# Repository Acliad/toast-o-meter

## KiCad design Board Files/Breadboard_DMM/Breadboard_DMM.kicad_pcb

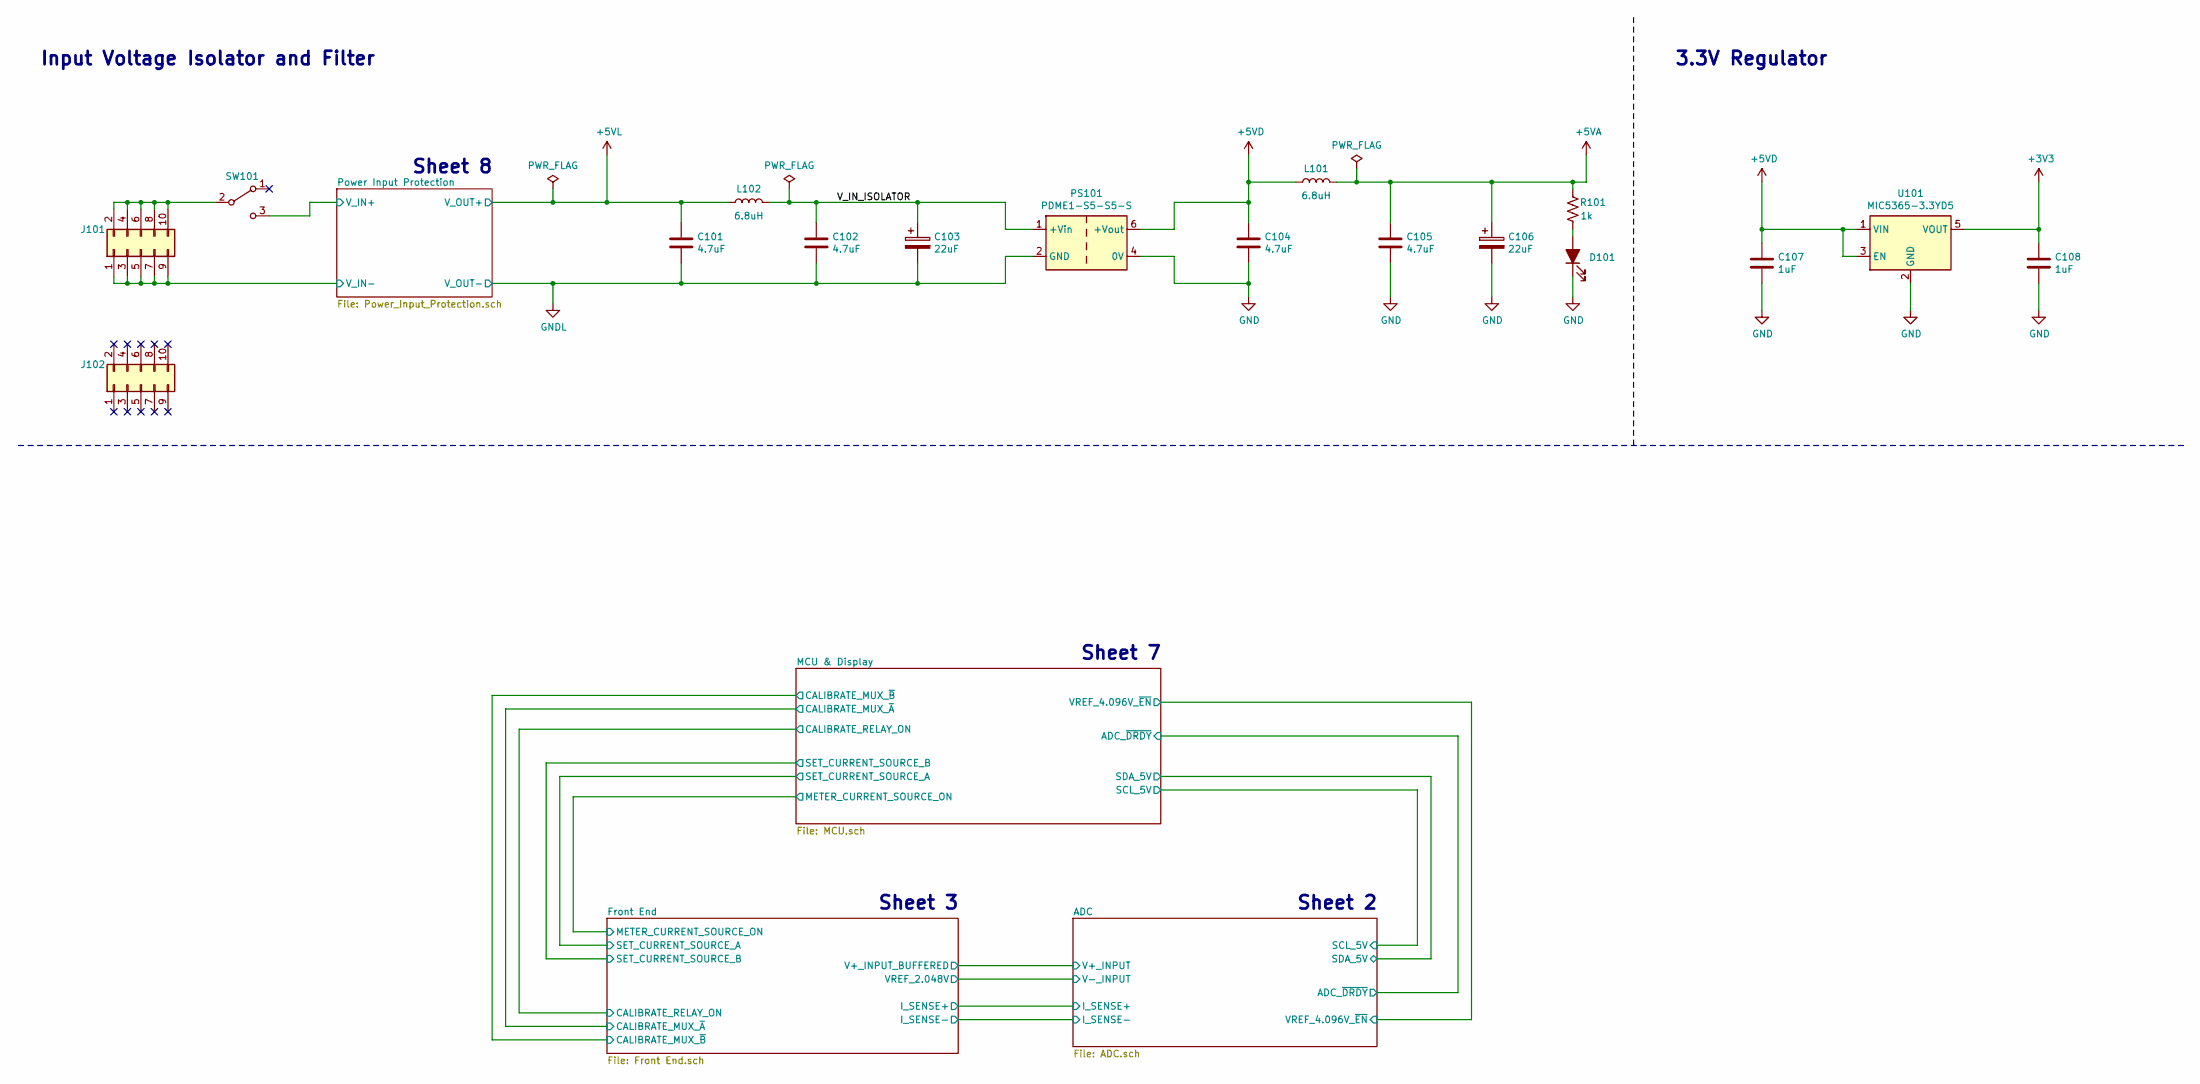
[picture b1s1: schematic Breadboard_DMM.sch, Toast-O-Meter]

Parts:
C101, C102, C104, C105: 4.7uF; C_0805_2012Metric_Pad1.18x1.45mm_HandSolder; Digi-Key PN 1276-6462-1-ND
C103, C106: 22uF; CP_Elec_5x5.3; Digi-Key PN 732-8505-1-ND
C107, C108: 1uF; C_0603_1608Metric_Pad1.08x0.95mm_HandSolder; Digi-Key PN 1276-6524-1-ND
D101: Pink; LED_Kingbright_AA3528V_3.5x2.8mm_handsolder; MPN AA3528VRVCS/A; Digi-Key PN 754-1534-1-ND
J101, J102: Conn_02x05_Odd_Even; PinHeader_2x05_P2.54mm_Vertical; Digi-Key PN 2057-PH2-10-UA-ND
L101, L102: 6.8uH; L_Taiyo-Yuden_NR-30xx_HandSoldering; Digi-Key PN 587-2592-1-ND
PS101: PDME1-S5-S5-S; CUI_DCDC-CONVERTER_PDME1-Sxx-S_1x4_P2.54mm_Drill1.0mm; MPN PDME1-S5-S5-S; Digi-Key PN 102-6320-ND
R101: 1k; R_0603_1608Metric_Pad1.05x0.95mm_HandSolder; Digi-Key PN 311-1.00KHRCT-ND
SW101: L102021ML04Q; SW_CuK_L102021ML04Q_SPDT_Angled; MPN L102021ML04Q; Digi-Key PN CKC5102-ND
U101: MIC5365-3.3YD5; SOT-23-5; Digi-Key PN 576-4085-1-ND

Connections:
+3V3: C108.1, U101.5 (VOUT); also elsewhere on the board
+5VA: C105.1, C106.1, L101.2, R101.1; also elsewhere on the board
+5VD: C104.1, C107.1, L101.1, PS101.6 (+Vout), U101.1 (VIN), U101.3 (EN); also elsewhere on the board
+5VL: C101.1, L102.1; also elsewhere on the board
/Power Input Protection/V_IN+: SW101.3 (C); also elsewhere on the board
/V_IN_ISOLATOR: C102.1, C103.1, L102.2, PS101.1 (+Vin)
GND: C104.2, C105.2, C106.2, C107.2, C108.2, D101.1 (K), PS101.4 (0V), U101.2 (GND); also elsewhere on the board
GNDL: C101.2, C102.2, C103.2, J101.1, J101.3, J101.5, J101.7, J101.9, PS101.2 (GND); also elsewhere on the board
unnamed: D101.2 (A), R101.2
unnamed: J101.2, J101.4, J101.6, J101.8, J101.10, SW101.2 (B)

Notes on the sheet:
Input Voltage Isolator and Filter
3.3V Regulator
Sheet 7
Sheet 2
Sheet 8
Sheet 3

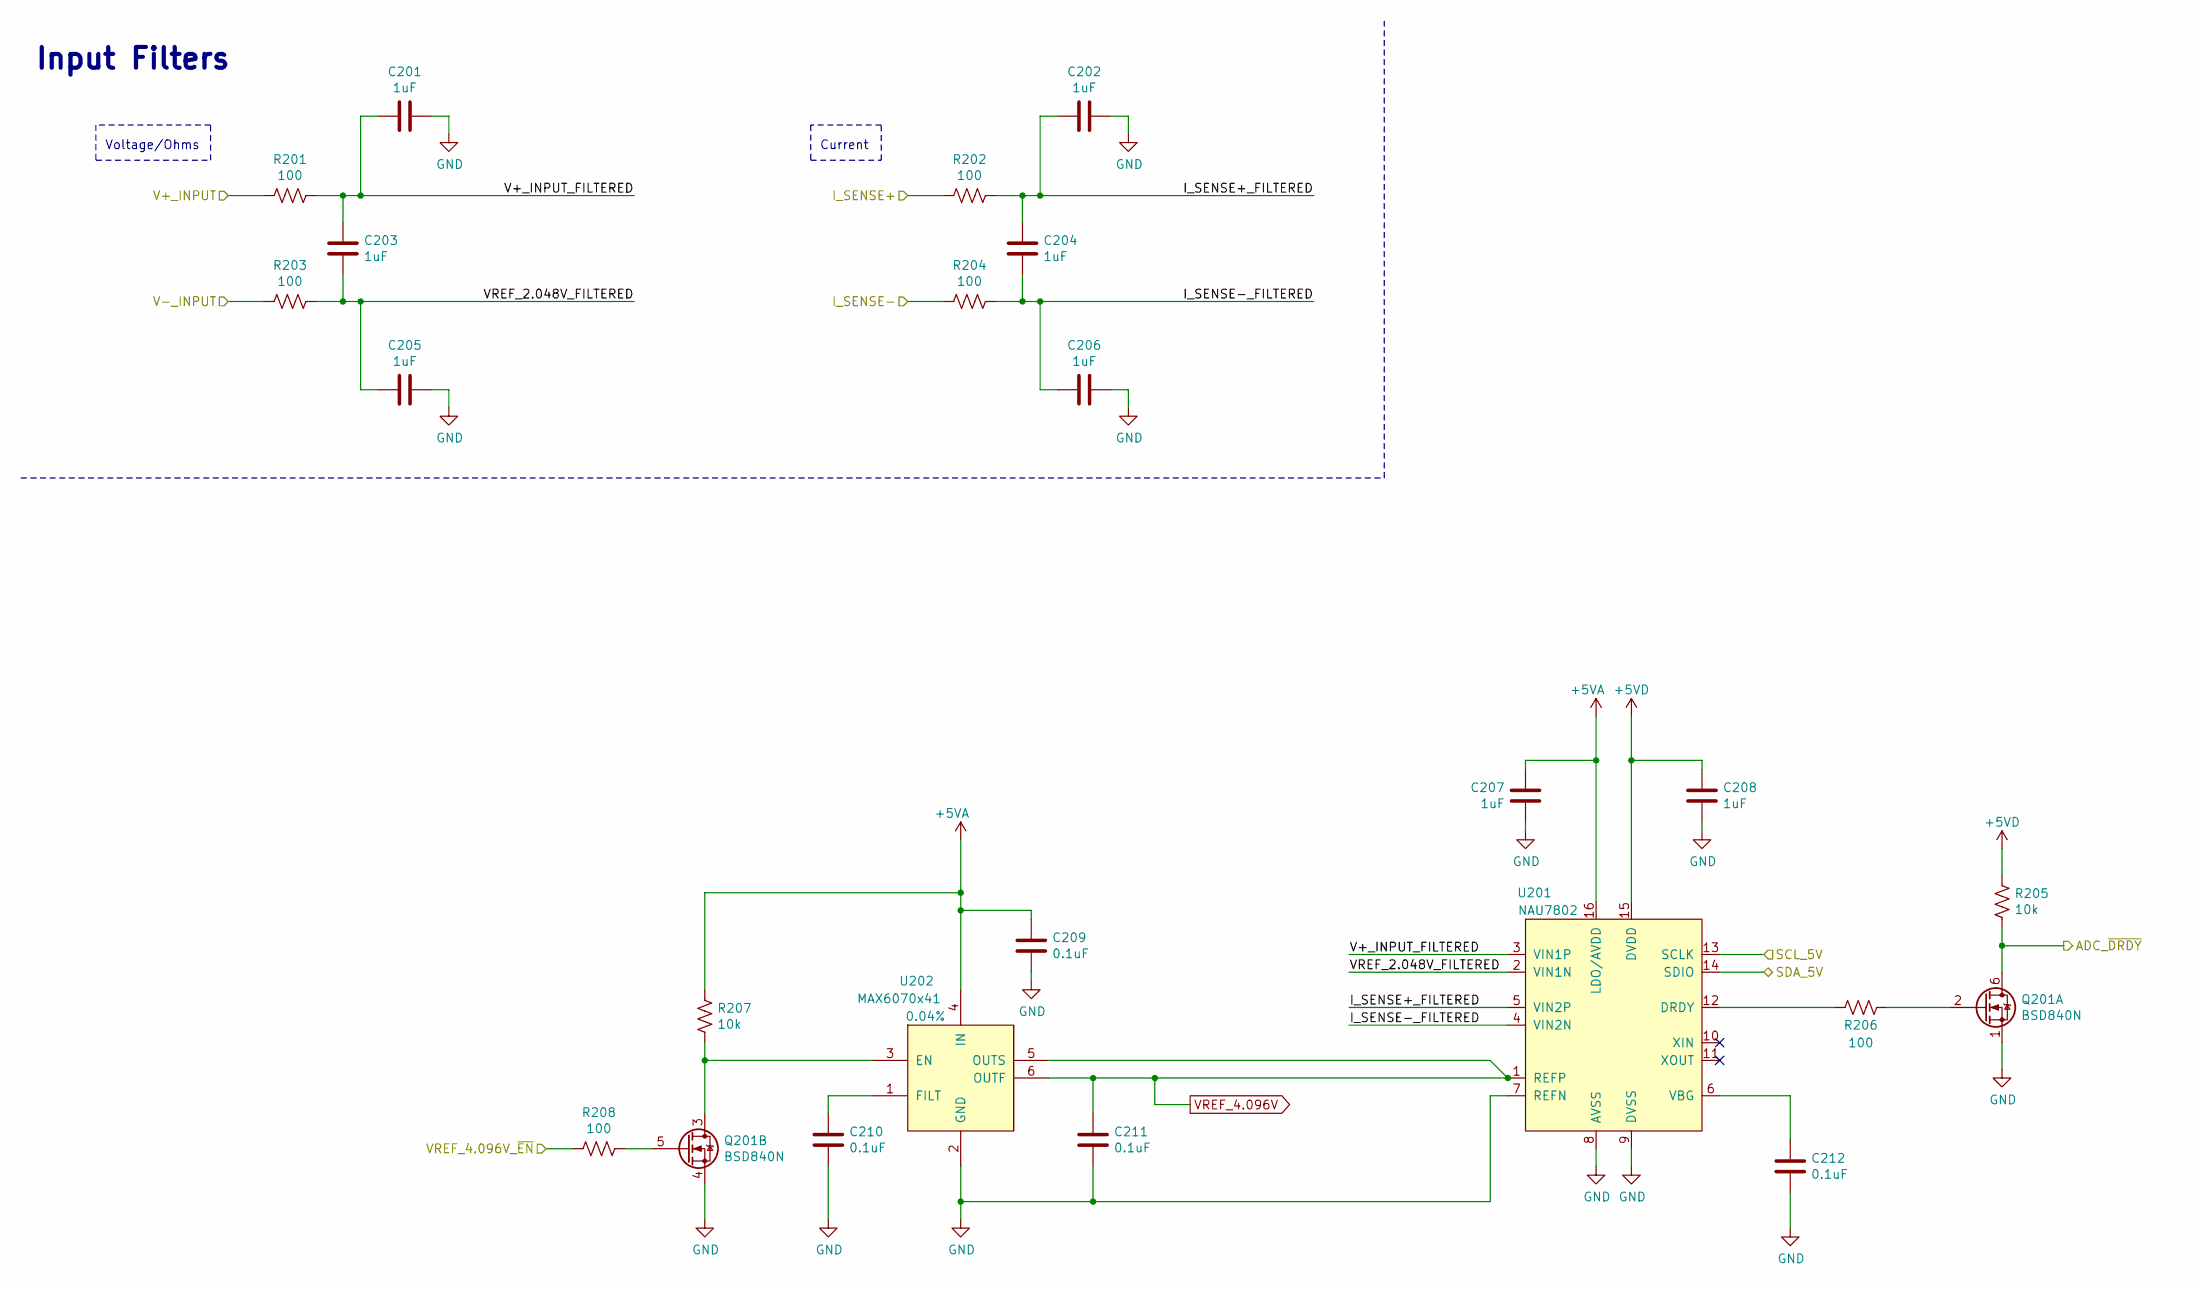
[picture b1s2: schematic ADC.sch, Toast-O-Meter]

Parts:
C201, C202, C203, C204, C205, C206, C207, C208: 1uF; C_0603_1608Metric_Pad1.08x0.95mm_HandSolder; Digi-Key PN 1276-6524-1-ND
C209, C210, C211, C212: 0.1uF; C_0603_1608Metric_Pad1.08x0.95mm_HandSolder; Digi-Key PN 1276-1006-1-ND
Q201: BSD840N; SOT-363_SC-70-6_Handsoldering; MPN BSD840NH6327XTSA1; Digi-Key PN BSD840NH6327XTSA1CT-ND
R201, R202, R203, R204, R206, R208: 100; R_0603_1608Metric_Pad1.05x0.95mm_HandSolder; Digi-Key PN 311-100HRCT-ND
R205, R207: 10k; R_0603_1608Metric_Pad1.05x0.95mm_HandSolder; Digi-Key PN 311-10.0KHRCT-ND
U201: NAU7802; SOP-16_4.55x10.3mm_P1.27mm; MPN NAU7802; Digi-Key PN NAU7802SGI-ND
U202: MAX6070x41; SOT-23-6; Tolerance 0.04%; Digi-Key PN MAX6070AAUT41+TCT-ND

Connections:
+5VA: C207.2, C209.1, R207.2, U201.16 (LDO/AVDD), U202.4 (IN); also elsewhere on the board
+5VD: C208.1, R205.2, U201.15 (DVDD); also elsewhere on the board
/ADC/ADC_~DRDY: Q201.6 (D1), R205.1; also elsewhere on the board
/ADC/I_SENSE+: R202.1; also elsewhere on the board
/ADC/I_SENSE+_FILTERED: C202.1, C204.1, R202.2, U201.5 (VIN2P)
/ADC/I_SENSE-: R204.1; also elsewhere on the board
/ADC/I_SENSE-_FILTERED: C204.2, C206.1, R204.2, U201.4 (VIN2N)
/ADC/SCL_5V: U201.13 (SCLK); also elsewhere on the board
/ADC/SDA_5V: U201.14 (SDIO); also elsewhere on the board
/ADC/V+_INPUT: R201.1; also elsewhere on the board
/ADC/V+_INPUT_FILTERED: C201.1, C203.1, R201.2, U201.3 (VIN1P)
/ADC/V-_INPUT: R203.1; also elsewhere on the board
/ADC/VREF_2.048V_FILTERED: C203.2, C205.1, R203.2, U201.2 (VIN1N)
/ADC/VREF_4.096V_~EN: R208.1; also elsewhere on the board
GND: C201.2, C202.2, C205.2, C206.2, C207.1, C208.2, C209.2, C210.2, C211.2, C212.2, Q201.1 (S1), Q201.4 (S2), U201.7 (REFN), U201.8 (AVSS), U201.9 (DVSS), U202.2 (GND); also elsewhere on the board
unnamed: C210.1, U202.1 (FILT)
unnamed: C212.1, U201.6 (VBG)
unnamed: Q201.2 (G1), R206.2
unnamed: Q201.3 (D2), R207.1, U202.3 (EN)
unnamed: Q201.5 (G2), R208.2
unnamed: R206.1, U201.12 (DRDY)
VREF_4.096V: C211.1, U201.1 (REFP), U202.5 (OUTS), U202.6 (OUTF); also elsewhere on the board

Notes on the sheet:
Input Filters
Current
Voltage/Ohms

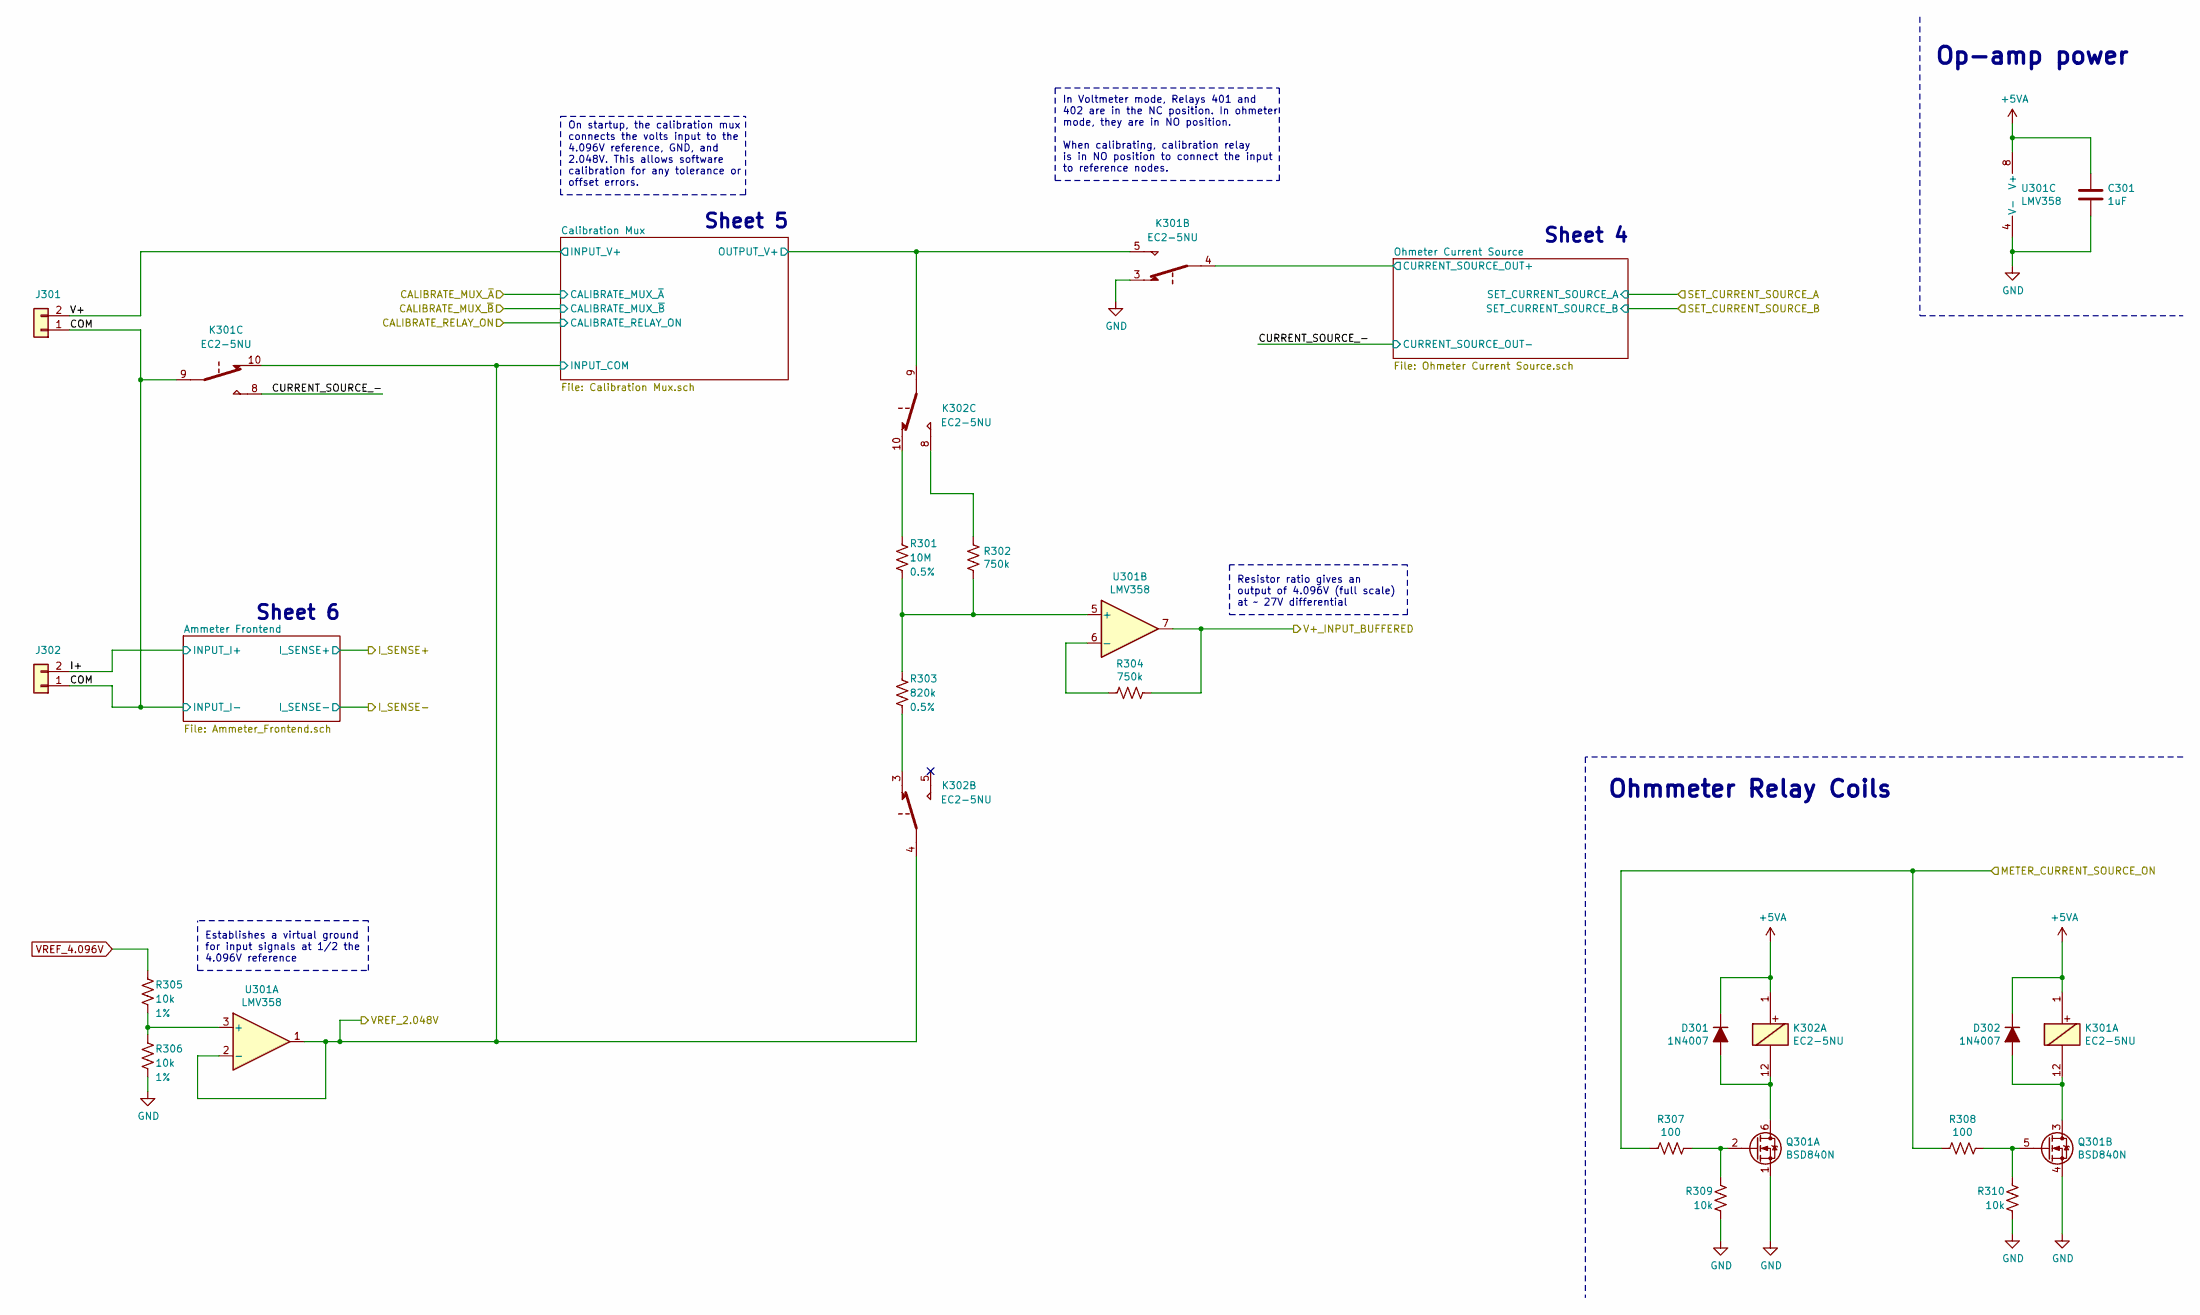
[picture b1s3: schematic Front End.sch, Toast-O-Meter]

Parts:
C301: 1uF; C_0603_1608Metric_Pad1.08x0.95mm_HandSolder; Digi-Key PN 1276-6524-1-ND
D301, D302: 1N4007; D_SOD-123; Digi-Key PN 1655-1N4007FLCT-ND
J301, J302: Conn_01x02; PinSocket_1x02_P2.54mm_Vertical; Digi-Key PN SAM1213-02-ND
K301, K302: EC2-5NU; Relay_DPDT_Kemet_EC2; MPN EC2-5NU; Digi-Key PN 399-11052-5-ND
Q301: BSD840N; SOT-363_SC-70-6_Handsoldering; MPN BSD840NH6327XTSA1; Digi-Key PN BSD840NH6327XTSA1CT-ND
R301: 10M; R_0603_1608Metric_Pad1.05x0.95mm_HandSolder; Tolerance 0.5%; Digi-Key PN 541-10MAYCT-ND
R302, R304: 750k; R_0603_1608Metric_Pad1.05x0.95mm_HandSolder; Digi-Key PN 311-750KHRCT-ND
R303: 820k; R_0805_2012Metric_Pad1.15x1.40mm_HandSolder; Tolerance 0.5%; Digi-Key PN RR12P820KDCT-ND
R305, R306: 10k; R_0603_1608Metric_Pad1.05x0.95mm_HandSolder; Tolerance 1%; Digi-Key PN 311-10.0KHRCT-ND
R307, R308: 100; R_0603_1608Metric_Pad1.05x0.95mm_HandSolder; Digi-Key PN 311-100HRCT-ND
R309, R310: 10k; R_0603_1608Metric_Pad1.05x0.95mm_HandSolder; Digi-Key PN 311-10.0KHRCT-ND
U301: LMV358; SOIC-8_3.9x4.9mm_P1.27mm; Digi-Key PN 296-47593-1-ND

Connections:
+5VA: C301.1, D301.1 (K), D302.1 (K), K301.1, K302.1, U301.8 (V+); also elsewhere on the board
/ADC/I_SENSE-: J301.1, J302.1, K301.9; also elsewhere on the board
/ADC/V+_INPUT: R304.1, U301.7; also elsewhere on the board
/ADC/V-_INPUT: K301.10, K302.4, U301.1, U301.2 (-); also elsewhere on the board
/Front End/CURRENT_SOURCE_-: K301.8; also elsewhere on the board
/Front End/Calibration Mux/OUTPUT_V+: K301.5, K302.9; also elsewhere on the board
/Front End/I+: J302.2; also elsewhere on the board
/Front End/METER_CURRENT_SOURCE_ON: R307.1, R308.1; also elsewhere on the board
/Front End/Ohmeter Current Source/CURRENT_SOURCE_OUT+: K301.4; also elsewhere on the board
/Front End/V+: J301.2; also elsewhere on the board
GND: C301.2, K301.3, Q301.1 (S1), Q301.4 (S2), R306.2, R309.2, R310.2, U301.4 (V-); also elsewhere on the board
unnamed: D301.2 (A), K302.12, Q301.6 (D1)
unnamed: D302.2 (A), K301.12, Q301.3 (D2)
unnamed: K302.3, R303.2
unnamed: K302.8, R302.1
unnamed: K302.10, R301.1
unnamed: Q301.2 (G1), R307.2, R309.1
unnamed: Q301.5 (G2), R308.2, R310.1
unnamed: R301.2, R302.2, R303.1, U301.5 (+)
unnamed: R304.2, U301.6 (-)
unnamed: R305.2, R306.1, U301.3 (+)
VREF_4.096V: R305.1; also elsewhere on the board

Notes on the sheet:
Resistor ratio gives an output of 4.096V (full scale) at ~~ 27V differential
In Voltmeter mode, Relays 401 and 402 are in the NC position. In ohmeter mode, they are in NO position. When calibrating, calibration relay is in NO position to connect the input to reference nodes.
On startup, the calibration mux connects the volts input to the 4.096V reference, GND, and 2.048V. This allows software calibration for any tolerance or offset errors.
Ohmmeter Relay Coils
Op-amp power
Sheet 6
Sheet 5
Sheet 4
Establishes a virtual ground for input signals at 1/2 the 4.096V reference

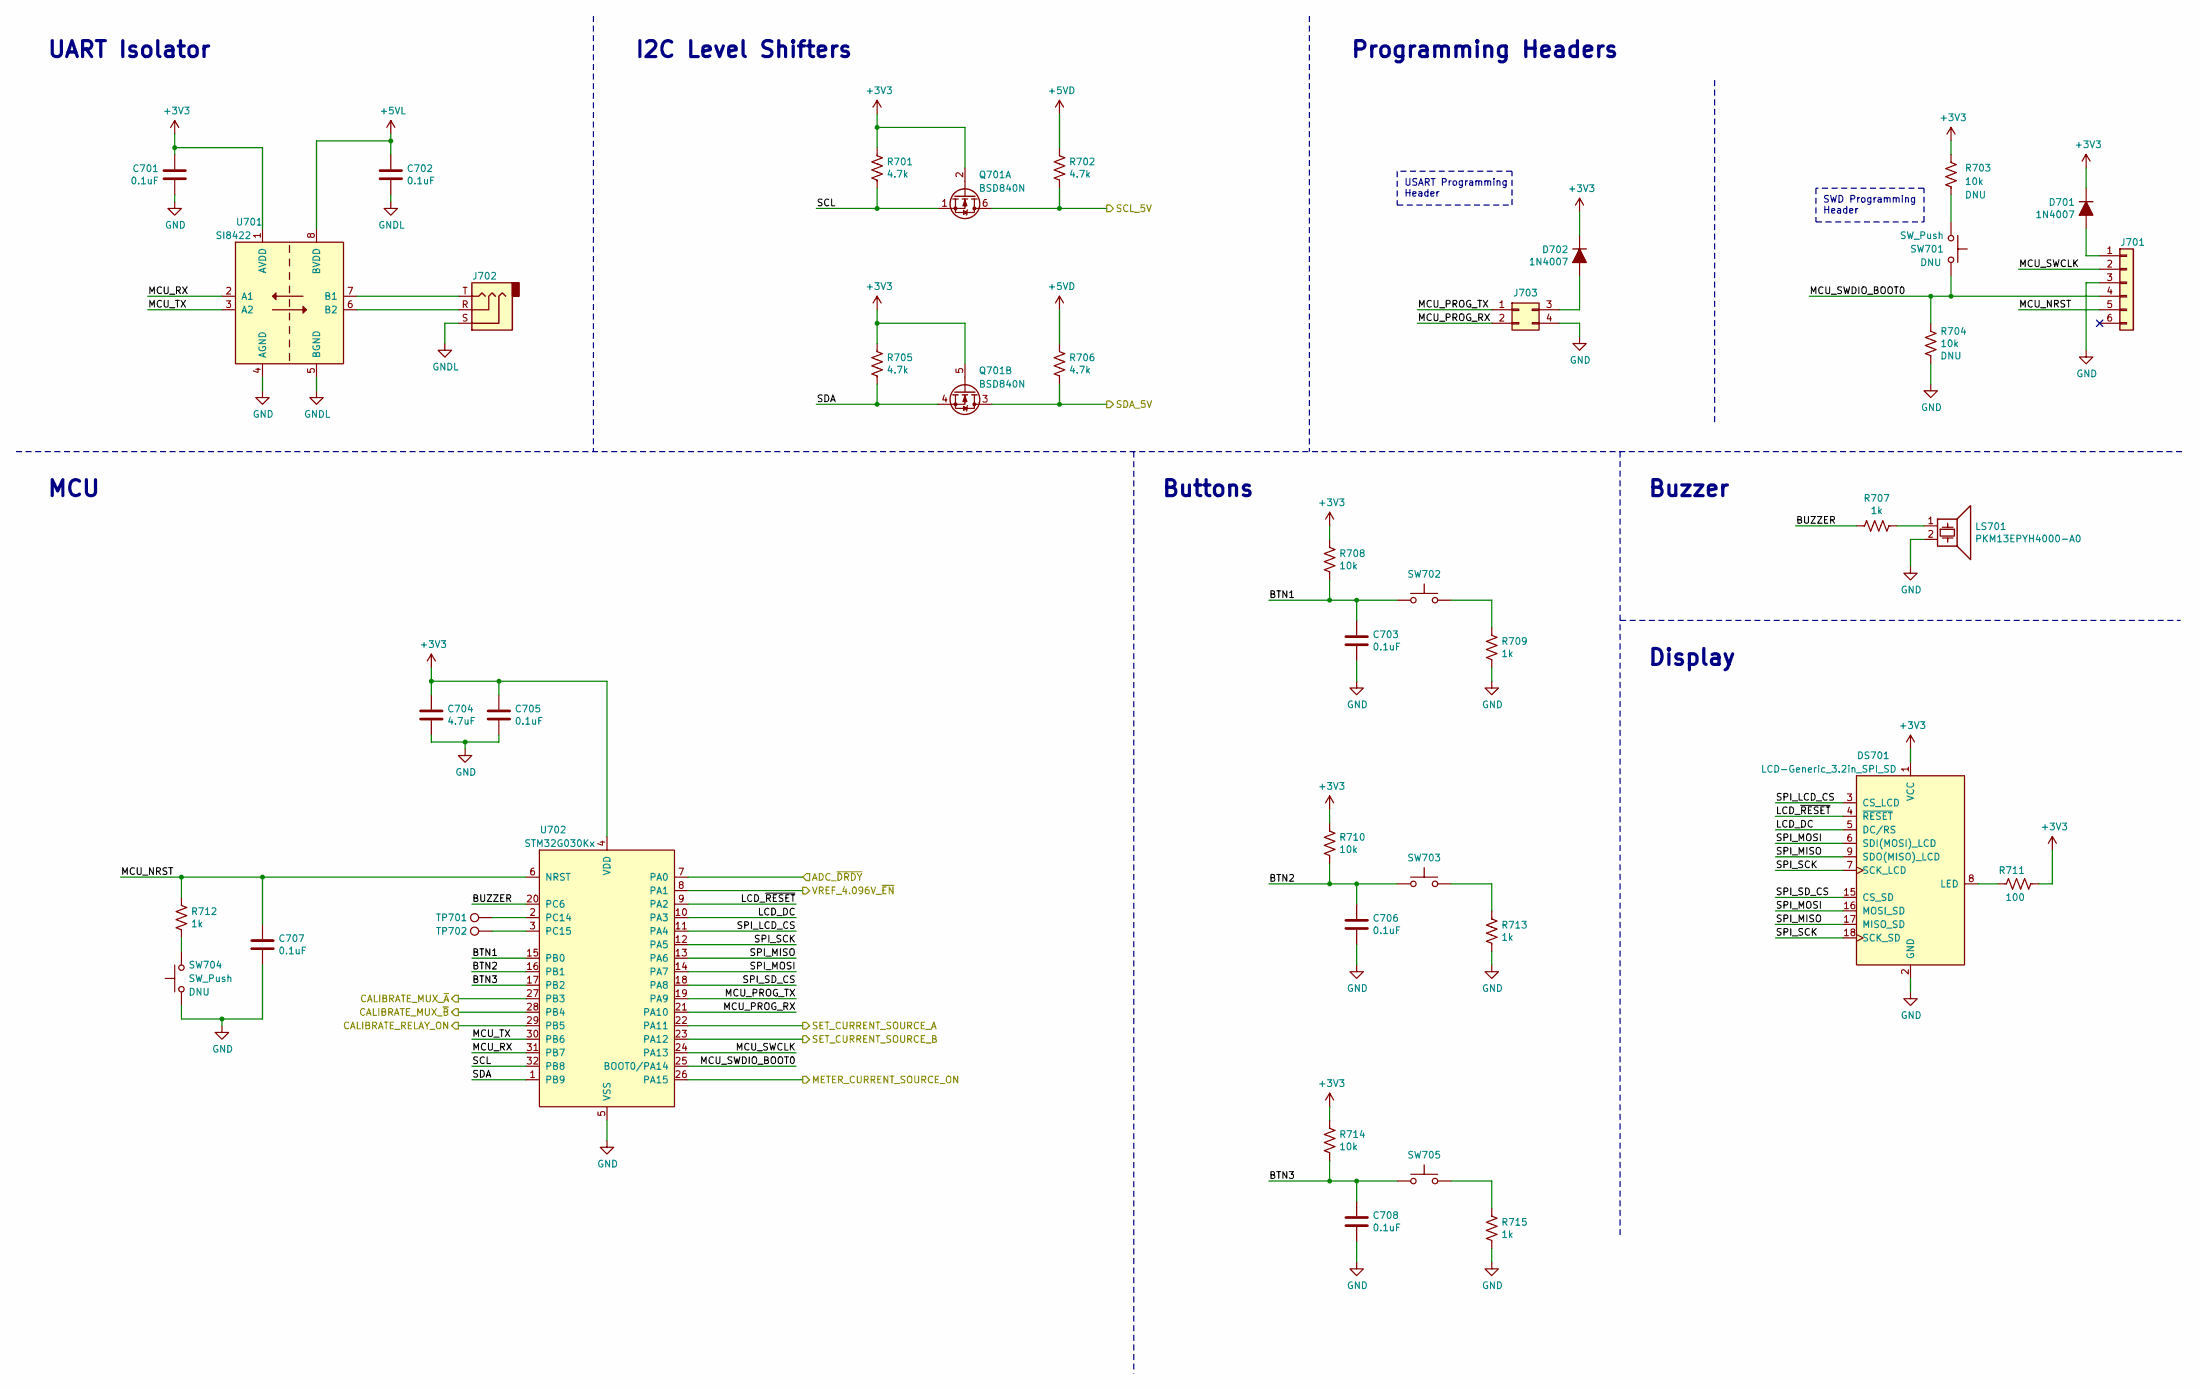
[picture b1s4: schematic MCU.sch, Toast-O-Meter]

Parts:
C701, C702, C703, C705, C706, C707, C708: 0.1uF; C_0603_1608Metric_Pad1.08x0.95mm_HandSolder; Digi-Key PN 1276-1006-1-ND
C704: 4.7uF; C_0805_2012Metric_Pad1.18x1.45mm_HandSolder; Digi-Key PN 1276-6462-1-ND
D701, D702: 1N4007; D_SOD-123; Digi-Key PN 1655-1N4007FLCT-ND
DS701: LCD-Generic_3.2in_SPI_SD; LCD-Generic-3.2in_89.30x55.04mm_ReducedCourtyard; Digi-Key PN SAM1093-04-ND; SAM1093-14-ND
J701: Conn_01x06; PinHeader_1x06_P2.54mm_Horizontal; Digi-Key PN 2057-PH1RA-06-UA-ND
J702: AudioJack3; Jack_3.5mm_CUI_SJ1-3523N_Horizontal; Digi-Key PN CP1-3523N-ND
J703: Conn_02x02_Top_Bottom; PinHeader_2x02_P2.54mm_Horizontal; Digi-Key PN 2057-PH2RA-04-UA-ND
LS701: PKM13EPYH4000-A0; Buzzer_Murata_PKM13EPYH4000-A0_D12.6mm_H6.9mm; MPN PKM13EPYH4000-A0; Digi-Key PN 490-4698-1-ND
Q701: BSD840N; SOT-363_SC-70-6_Handsoldering; MPN BSD840NH6327XTSA1; Digi-Key PN BSD840NH6327XTSA1CT-ND
R701, R702, R705, R706: 4.7k; R_0603_1608Metric_Pad1.05x0.95mm_HandSolder; Digi-Key PN 311-4.70KHRCT-ND
R703, R704, R708, R710, R714: 10k; R_0603_1608Metric_Pad1.05x0.95mm_HandSolder; Digi-Key PN 311-10.0KHRCT-ND
R707, R709, R712, R713, R715: 1k; R_0603_1608Metric_Pad1.05x0.95mm_HandSolder; Digi-Key PN 311-1.00KHRCT-ND
R711: 100; R_0603_1608Metric_Pad1.05x0.95mm_HandSolder; Digi-Key PN 311-100HRCT-ND
SW701, SW704: SW_Push; SW-PUSH-6x3.5mm_CK-PTS636SL43x_HandSolder; Digi-Key PN CKN12309-1-ND
SW702, SW703, SW705: SW_Push; SW_PUSH-12mm_Wuerth-430476085716_HandSolder; Digi-Key PN 732-13655-1-ND
TP701, TP702: TestPoint; TestPoint_THTPad_D1.5mm_Drill0.7mm; Digi-Key PN 2057-PH2-10-UA-ND
U701: SI8422; SOIC-8_3.9x4.9mm_P1.27mm; Digi-Key PN SI8422AB-D-IS-ND
U702: STM32G030Kx; LQFP-32_7x7mm_P0.8mm; Digi-Key PN 497-19769-ND

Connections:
+3V3: C701.1, C704.1, C705.1, D701.1 (K), D702.1 (K), DS701.1 (VCC), Q701.2 (G1), Q701.5 (G2), R701.1, R703.1, R705.1, R708.1, R710.1, R711.2, R714.1, U701.1 (AVDD), U702.4 (VDD); also elsewhere on the board
+5VD: R702.1, R706.1; also elsewhere on the board
+5VL: C702.1, U701.8 (BVDD); also elsewhere on the board
/ADC/ADC_~DRDY: U702.7 (PA0); also elsewhere on the board
/ADC/SCL_5V: Q701.6 (D1), R702.2; also elsewhere on the board
/ADC/SDA_5V: Q701.3 (D2), R706.2; also elsewhere on the board
/ADC/VREF_4.096V_~EN: U702.8 (PA1); also elsewhere on the board
/Front End/CALIBRATE_MUX_~A: U702.27 (PB3); also elsewhere on the board
/Front End/CALIBRATE_MUX_~B: U702.28 (PB4); also elsewhere on the board
/Front End/CALIBRATE_RELAY_ON: U702.29 (PB5); also elsewhere on the board
/Front End/METER_CURRENT_SOURCE_ON: U702.26 (PA15); also elsewhere on the board
/Front End/SET_CURRENT_SOURCE_A: U702.22 (PA11); also elsewhere on the board
/Front End/SET_CURRENT_SOURCE_B: U702.23 (PA12); also elsewhere on the board
/MCU & Display/BTN1: C703.1, R708.2, SW702.1, U702.15 (PB0)
/MCU & Display/BTN2: C706.1, R710.2, SW703.1, U702.16 (PB1)
/MCU & Display/BTN3: C708.1, R714.2, SW705.1, U702.17 (PB2)
/MCU & Display/BUZZER: R707.1, U702.20 (PC6)
/MCU & Display/LCD_DC: DS701.5 (DC/RS), U702.10 (PA3)
/MCU & Display/LCD_~RESET~: DS701.4 (~RESET), U702.9 (PA2)
/MCU & Display/MCU_NRST: C707.1, J701.5, R712.1, U702.6 (NRST)
/MCU & Display/MCU_PROG_RX: J703.2, U702.21 (PA10)
/MCU & Display/MCU_PROG_TX: J703.1, U702.19 (PA9)
/MCU & Display/MCU_RX: U701.2 (A1), U702.31 (PB7)
/MCU & Display/MCU_SWCLK: J701.2, U702.24 (PA13)
/MCU & Display/MCU_SWDIO_BOOT0: J701.4, R704.1, SW701.2, U702.25 (BOOT0/PA14)
/MCU & Display/MCU_TX: U701.3 (A2), U702.30 (PB6)
/MCU & Display/SCL: Q701.1 (S1), R701.2, U702.32 (PB8)
/MCU & Display/SDA: Q701.4 (S2), R705.2, U702.1 (PB9)
/MCU & Display/SPI_LCD_CS: DS701.3 (CS_LCD), U702.11 (PA4)
/MCU & Display/SPI_MISO: DS701.9 (SDO(MISO)_LCD), DS701.17 (MISO_SD), U702.13 (PA6)
/MCU & Display/SPI_MOSI: DS701.6 (SDI(MOSI)_LCD), DS701.16 (MOSI_SD), U702.14 (PA7)
/MCU & Display/SPI_SCK: DS701.7 (SCK_LCD), DS701.18 (SCK_SD), U702.12 (PA5)
/MCU & Display/SPI_SD_CS: DS701.15 (CS_SD), U702.18 (PA8)
GND: C701.2, C703.2, C704.2, C705.2, C706.2, C707.2, C708.2, DS701.2 (GND), J701.3, J703.4, LS701.2, R704.2, R709.2, R713.2, R715.2, SW704.1, U701.4 (AGND), U702.5 (VSS); also elsewhere on the board
GNDL: C702.2, J702.S, U701.5 (BGND); also elsewhere on the board
unnamed: D701.2 (A), J701.1
unnamed: D702.2 (A), J703.3
unnamed: DS701.8 (LED), R711.1
unnamed: J702.R, U701.6 (B2)
unnamed: J702.T, U701.7 (B1)
unnamed: LS701.1, R707.2
unnamed: R703.2, SW701.1
unnamed: R709.1, SW702.2
unnamed: R712.2, SW704.2
unnamed: R713.1, SW703.2
unnamed: R715.1, SW705.2
unnamed: TP701.1, U702.2 (PC14)
unnamed: TP702.1, U702.3 (PC15)

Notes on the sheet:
USART Programming Header
SWD Programming Header
Programming Headers
MCU
I2C Level Shifters
UART Isolator
Buttons
Display
Buzzer

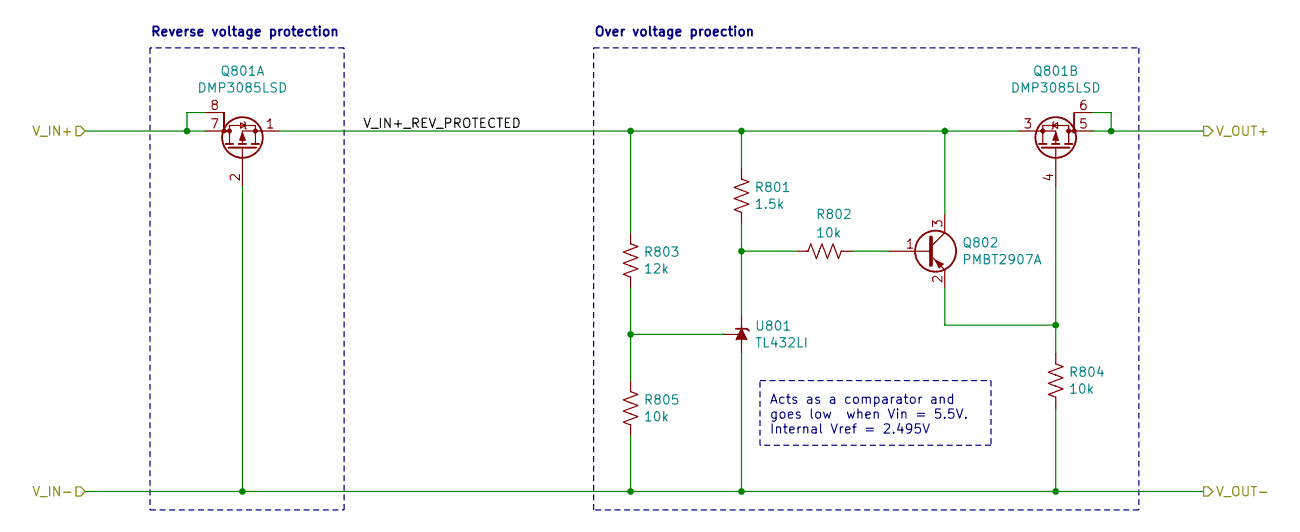
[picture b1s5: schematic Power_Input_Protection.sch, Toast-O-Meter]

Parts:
Q801: DMP3085LSD; SO-8_3.9x4.9mm_P1.27mm; MPN DMP3085LSD; Digi-Key PN DMP3085LSD-13DICT-ND
Q802: PMBT2907A; SOT-23_Handsoldering; MPN PMBT2907A; Digi-Key PN 1727-2958-1-ND
R801: 1.5k; R_0603_1608Metric_Pad1.05x0.95mm_HandSolder; Digi-Key PN 311-1.50KHRCT-ND
R802, R804, R805: 10k; R_0603_1608Metric_Pad1.05x0.95mm_HandSolder; Digi-Key PN 311-10.0KHRCT-ND
R803: 12k; R_0603_1608Metric_Pad1.05x0.95mm_HandSolder; Digi-Key PN 311-12.0KHRCT-ND
U801: TL432LI; SOT-23; MPN TL432LI; Digi-Key PN 296-53244-1-ND

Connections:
+5VL: Q801.5 (D), Q801.6 (G); also elsewhere on the board
/Power Input Protection/V_IN+: Q801.7 (D), Q801.8 (G); also elsewhere on the board
/Power Input Protection/V_IN+_REV_PROTECTED: Q801.1 (S), Q801.3 (S), Q802.3 (C), R801.2, R803.2
GNDL: Q801.2 (G), R804.1, R805.1, U801.3 (A); also elsewhere on the board
unnamed: Q801.4 (G), Q802.2 (E), R804.2
unnamed: Q802.1 (B), R802.1
unnamed: R801.1, R802.2, U801.1 (K)
unnamed: R803.1, R805.2, U801.2 (REF)

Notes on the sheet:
Reverse voltage protection
Over voltage proection
Acts as a comparator and goes low when Vin = 5.5V. Internal Vref = 2.495V
